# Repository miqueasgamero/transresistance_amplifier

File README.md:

# transresistance_amplifier

Un amplificador de los mil demonios.

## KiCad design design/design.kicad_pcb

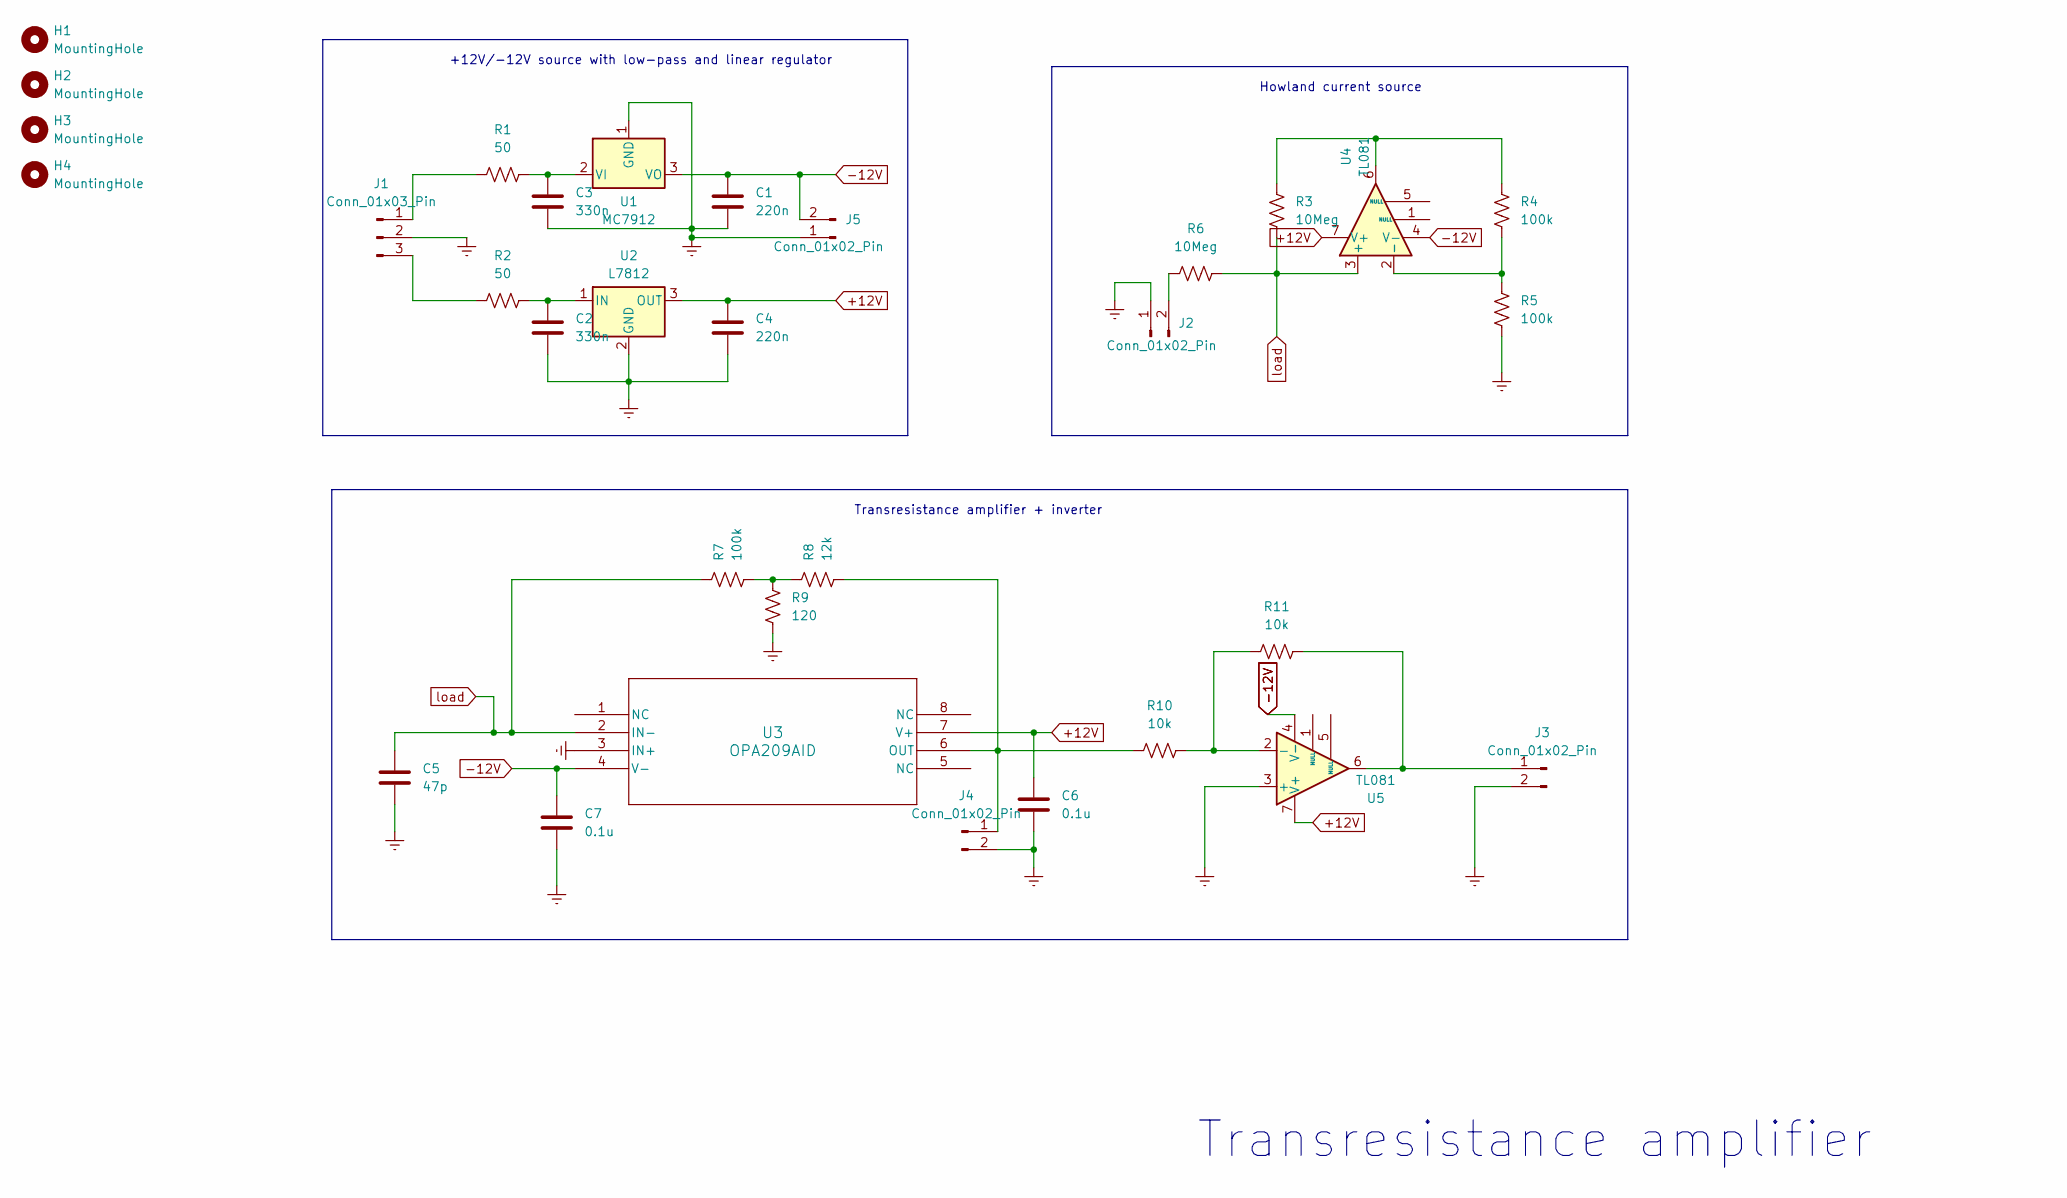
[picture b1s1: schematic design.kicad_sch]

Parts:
C1, C4: 220n; C_Disc_D6.0mm_W2.5mm_P5.00mm
C2, C3: 330n; C_Disc_D6.0mm_W2.5mm_P5.00mm
C5: 47p; C_0805_2012Metric_Pad1.18x1.45mm_HandSolder
C6, C7: 0.1u; C_0805_2012Metric_Pad1.18x1.45mm_HandSolder
H1, H2, H3, H4: MountingHole; MountingHole_3.5mm
J1: Conn_01x03_Pin; PinHeader_1x03_P2.54mm_Vertical
J2, J3, J4, J5: Conn_01x02_Pin; PinHeader_1x02_P2.54mm_Vertical
R1, R2: 50; R_Axial_DIN0204_L3.6mm_D1.6mm_P7.62mm_Horizontal
R3, R6: 10Meg; R_Axial_DIN0204_L3.6mm_D1.6mm_P7.62mm_Horizontal
R4, R5, R7: 100k; R_Axial_DIN0204_L3.6mm_D1.6mm_P7.62mm_Horizontal
R8: 12k; R_Axial_DIN0204_L3.6mm_D1.6mm_P7.62mm_Horizontal
R9: 120; R_Axial_DIN0204_L3.6mm_D1.6mm_P7.62mm_Horizontal
R10, R11: 10k; R_Axial_DIN0204_L3.6mm_D1.6mm_P7.62mm_Horizontal
U1: MC7912; TO-263-3_TabPin2
U2: L7812; TO-252-3_TabPin2
U3: OPA209AID; D8
U4, U5: TL081; DIP-8_W7.62mm_LongPads

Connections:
+12V: C4.1, C6.1, U2.3 (OUT), U3.7 (V+), U4.7 (V+), U5.7 (V+)
-12V: C1.1, C7.1, J5.2, U1.3 (VO), U3.4 (V-), U4.4 (V-), U5.4 (V-)
Earth: C1.2, C2.2, C3.2, C4.2, C5.2, C6.2, C7.2, J1.2, J2.1, J3.2, J4.2, J5.1, R5.1, R9.2, U1.1 (GND), U2.2 (GND), U3.3 (IN+), U5.3 (+)
unnamed: J1.1, R1.2
unnamed: J1.3, R2.1
unnamed: J2.2, R6.2
unnamed: J3.1, R11.1, U5.6
unnamed: J4.1, R8.1, R10.2, U3.6 (OUT)
unnamed: R3.2, R4.2, U4.6
unnamed: R7.1, R8.2, R9.1
unnamed: C3.1, R1.1, U1.2 (VI)
unnamed: C2.1, R2.2, U2.1 (IN)
unnamed: R4.1, R5.2, U4.2 (-)
unnamed: R10.1, R11.2, U5.2 (-)
load: C5.1, R3.1, R6.1, R7.2, U3.2 (IN-), U4.3 (+)

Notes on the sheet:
Transresistance amplifier
+12V/-12V source with low-pass and linear regulator
Howland current source
Transresistance amplifier + inverter

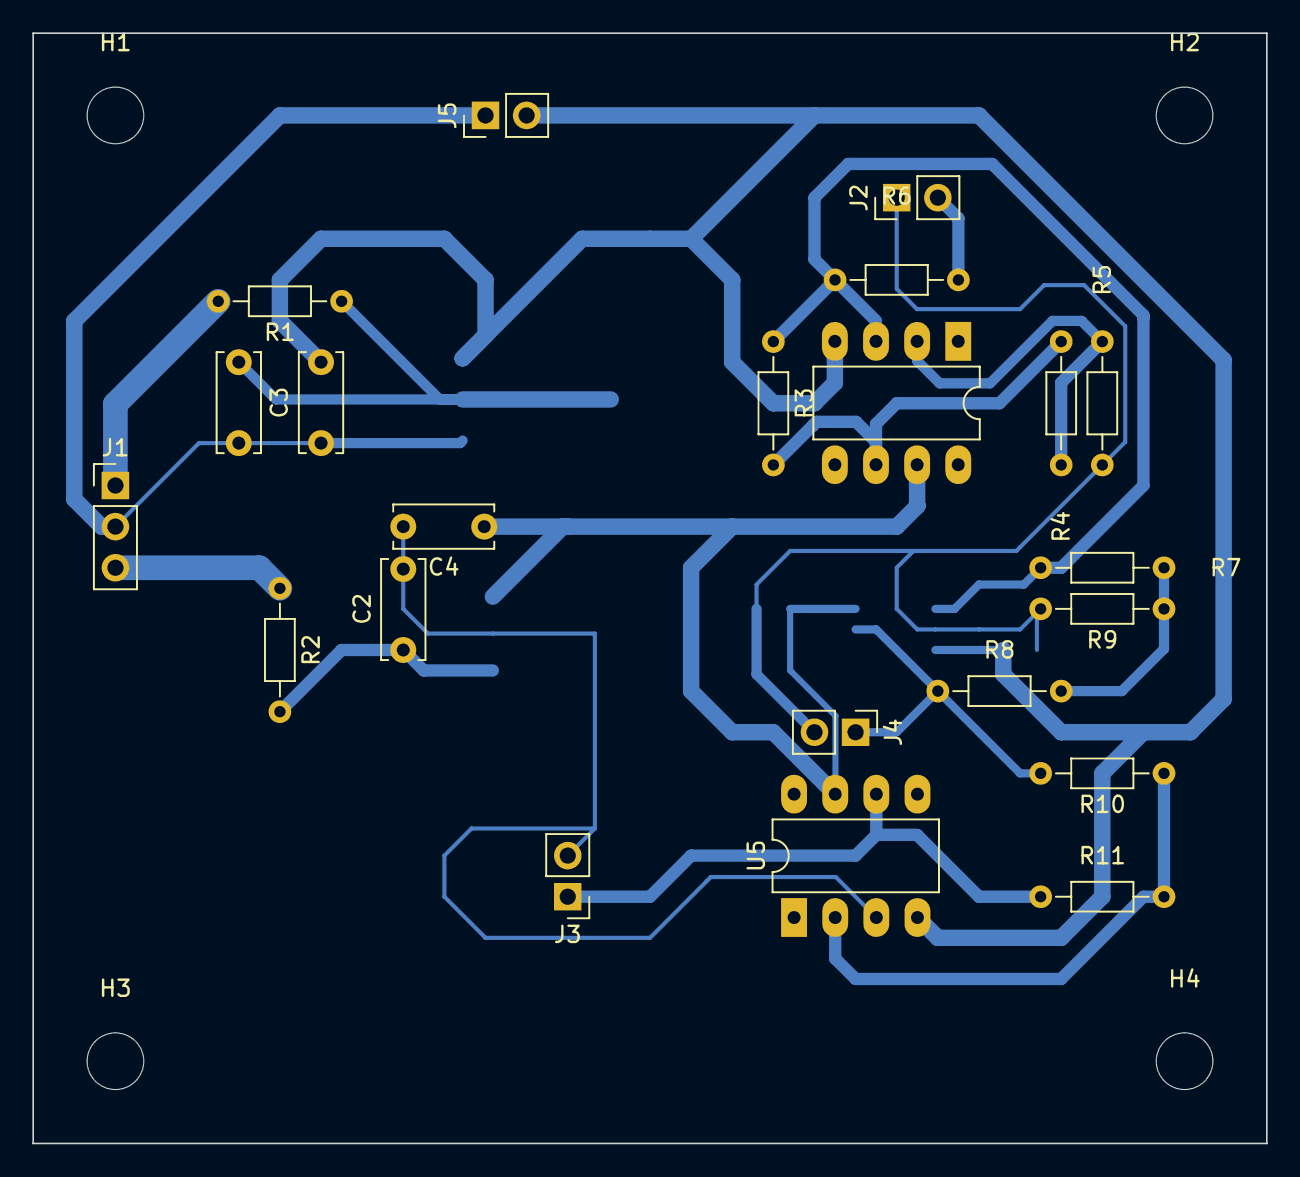
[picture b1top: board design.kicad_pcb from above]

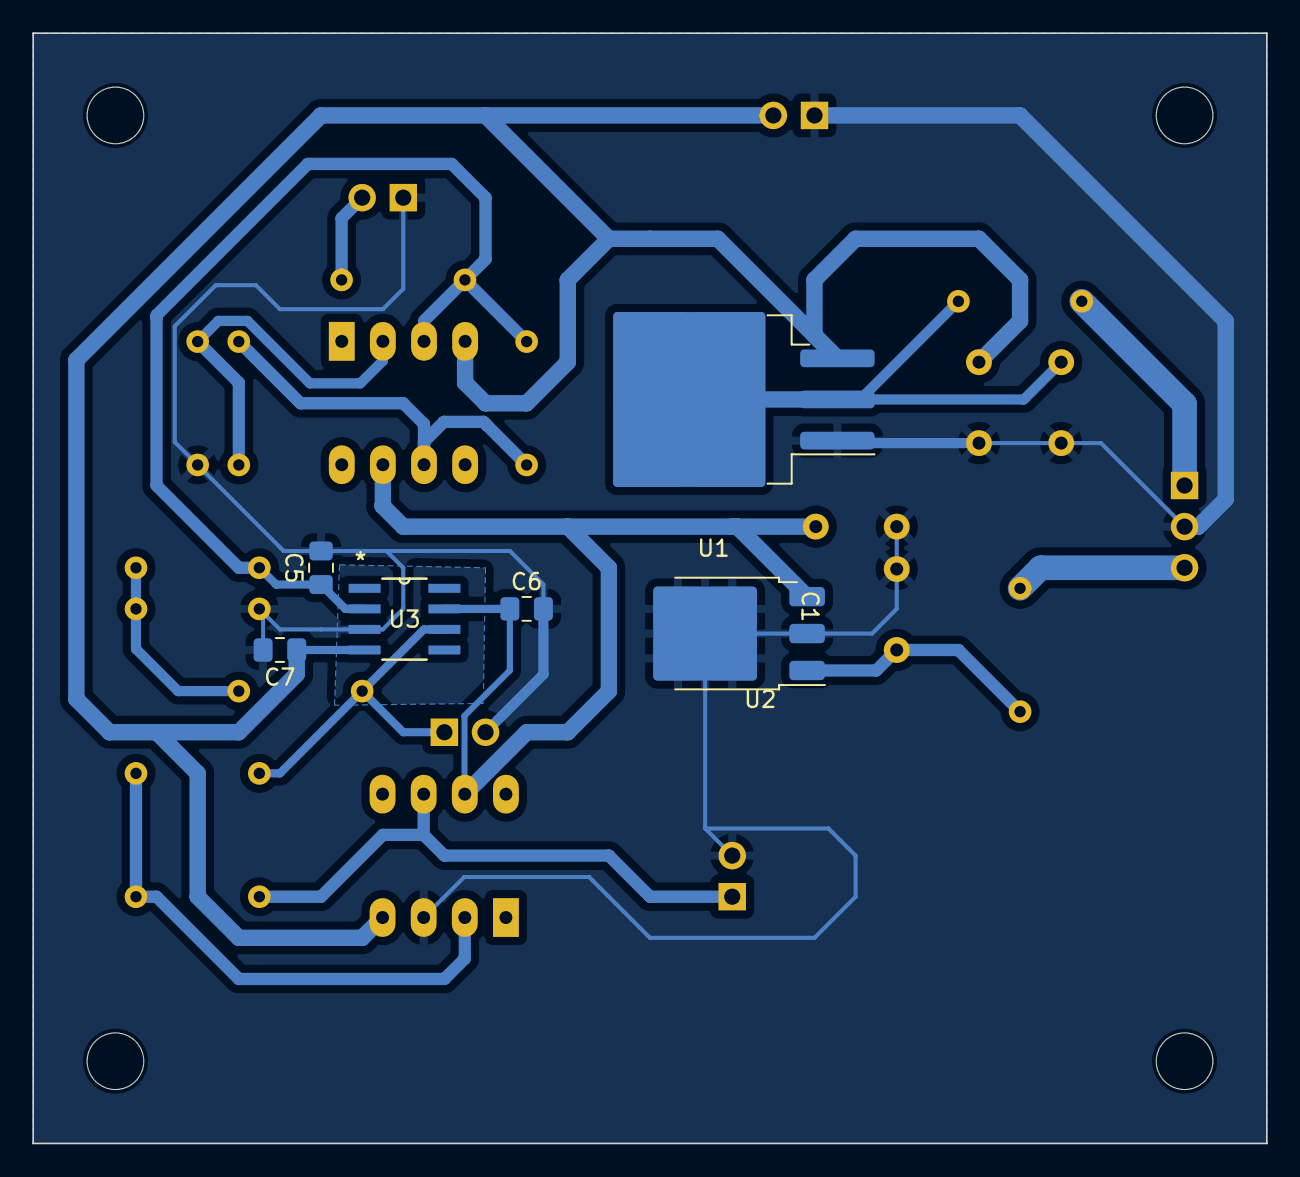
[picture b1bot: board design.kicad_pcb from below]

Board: 2 copper layers, 76.2 x 68.6 mm, 32 parts (6 on the bottom side), 15 nets.

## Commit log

2023-11-07 First commit. All added
2023-11-07 Modifiqué la simu
    Agregué una fuente de corriente
2023-11-07 Modifique la simulacion
2023-11-07 Create amplifier.asc
    Creé el archivo amplifier
2023-11-07 Simulacion de fuente Howlland con TL081 y UniversalOpAmp
2023-11-08 Regulador
    Hice el regulador de tensión
2023-11-08 Regulador de tensión negativa
    No encontré el modelo del LM337 en spice así que usé uno que encontré en internet. La simu anda así que usando la resistencia de 120 ohm que sugiere el datasheet alimentando con -16v y con una r2 de 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
2023-11-08 LM337
    ESTE es el modelo de spice que encontré!
2023-11-09 Modificaciones
2023-11-09 Agregue modelo del OPAx209. Acordate del .lib o .inc si lo vas a usar.
2023-11-11 Datasheets agregados
2023-11-11 Saque los Zone.Identifier
2023-11-11 Modelos
2023-11-11 Reguladores 78 y 79
2023-11-11 Respuesta en frecuencia de los reguladores
    La del primer regulador anda bien (corta en 10K) pero la del segundo atenúa demasiado y no corta bien
2023-11-11 corrección
    En la versión anterior ambas salidas de los reguladores tenían el mismo tag, lo cual confunde al simulador (creo). cuando se los cambié, veo que el regulador negativo atenía mucho y no corta en 10k. 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
2023-11-13 Nuevo datasheet
2023-11-13 Todo arreglado
2023-11-13 reguladores
2023-11-21 ultima
2023-11-21 buffer
2023-11-22 Modificando algunas simulaciones para compensacion en frecuencia
2023-11-22 Agregue la simulacion final
2023-11-22 Los reguladores ya estan en KiCad. Falta elegir footprint the capacitores
2023-11-22 Algunos datasheet nuevos
2023-11-22 Corregi errores
2023-11-23 Cambios muy importantes en PCB y schematic de KiCad
2023-11-25 Resolvi un problema con la simulacion amplifier. Por favor ponerle TL081 en campo Value
2023-11-27 Estan todos los ruteos hechos y DRC verificado. Falta engrosar tracks para mayores 10mils y agregar ground plane
2023-11-27 Agregado planos de masa y corregidos caminos para evitar capacidades parasitas en realimentaciones. Falta verificar con Ale
2023-11-27 Borre el plano de masa sobre Front Layer F.Cu porque era innecesario.
2023-11-27 Version final, archivos Gerber exportados y enviados
2023-12-09 Resolved conflicts?
2023-12-09 Se modificaron las simulaciones de rta en frecuencia con los TL081 y nueva ganancia
2023-12-09 Agregue la prueba de concepto avanzada (#2) en amplifier_new y la compensacion en frecuencia para la prueba #1
